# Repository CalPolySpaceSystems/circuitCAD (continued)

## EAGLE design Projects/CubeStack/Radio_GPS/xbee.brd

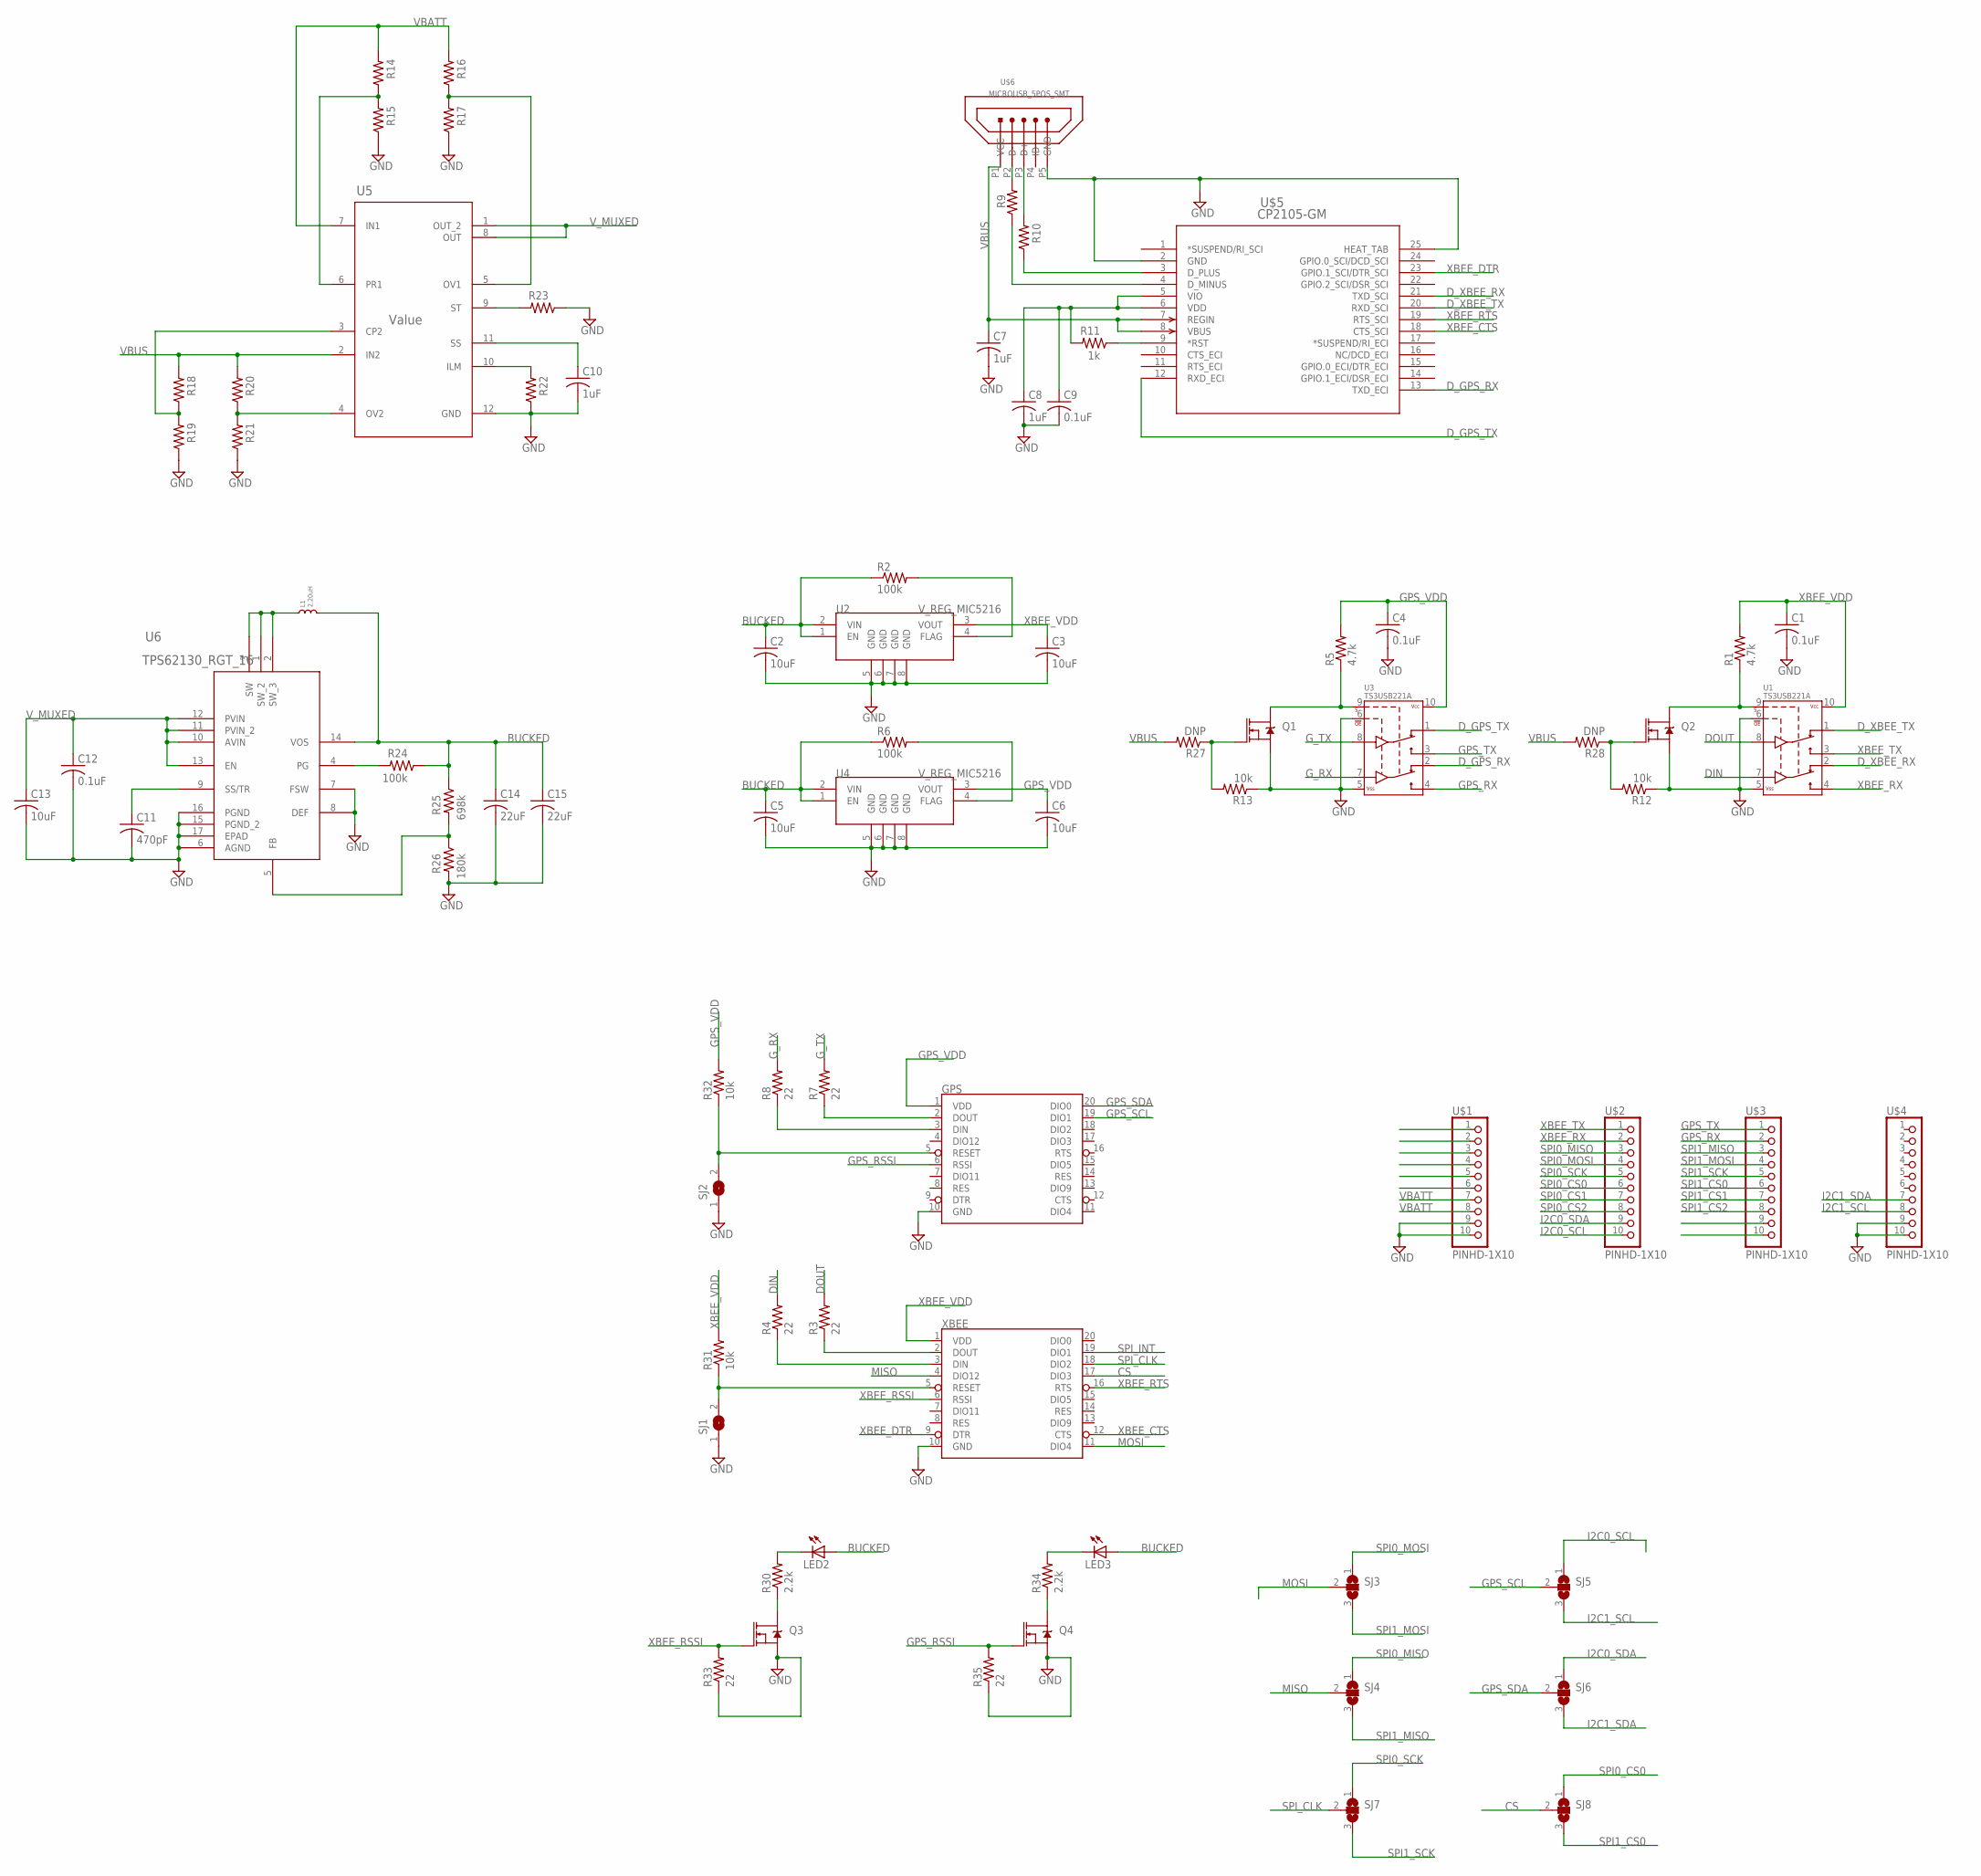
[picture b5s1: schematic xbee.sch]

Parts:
C1, C4, C9: 0.1uF; C0402
C2, C3, C5, C6, C13: 10uF; C1206
C7, C8, C10: 1uF; C0402
C11: 470pF; C0402
C12: 0.1uF; C0603
C14, C15: 22uF; C1210
GPS: XBEESMD; XBEE-SMD
L1: 2.20uH; XAL4020
LED2, LED3: LEDSML0603; SML0603
Q1, Q2, Q3, Q4: 310mA/60V/1.6Ω; SOT323
R1, R5: 4.7k; R0402
R2, R6, R24: 100k; R0402
R3, R4, R7, R8, R33, R35: 22; R0402
R9, R10, R14, R15, R16, R17, R18, R19, R20, R21, R22, R23: R-US_R0402; R0402
R11: 1k; R0402
R12, R13, R31, R32: 10k; R0402
R25: 698k; R0402
R26: 180k; R0402
R27, R28: DNP; R0402
R30, R34: 2.2k; R0402
SJ1, SJ2: SJW
SJ3, SJ4, SJ5, SJ6, SJ7, SJ8: SJ2W; SJ_2
U1, U3: TS3USB221A; QFN-10-RSE
U2, U4: V_REG_MIC5216; MSOP8
U5: Value; RUX0012A
U6: TPS62130_RGT_16; RGT16_1P7X1P7
U$1, U$2, U$3, U$4: PINHD-1X10; 1X10-BIG
U$5: CP2105-GM; QFN24_4X4
U$6: MICROUSB_5POS_SMT; RECPT_SMT_R/A
XBEE: XBEESMD; XBEE-SMD

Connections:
BUCKED: C2.1, C5.1, C14.1, C15.1, L1.2, LED2.A, LED3.A, R2.1, R6.1, R24.1, R25.1, U2.1 (EN), U2.2 (VIN), U4.1 (EN), U4.2 (VIN), U6.14 (VOS)
CS: SJ8.2, XBEE.17 (DIO3)
DIN: R4.2, U1.7 (D-)
DOUT: R3.2, U1.8 (D+)
D_GPS_RX: U3.2 (1D-), U$5.13 (TXD_ECI)
D_GPS_TX: U3.1 (1D+), U$5.12 (RXD_ECI)
D_XBEE_RX: U1.2 (1D-), U$5.21 (TXD_SCI)
D_XBEE_TX: U1.1 (1D+), U$5.20 (RXD_SCI)
GND: C1.2, C2.2, C3.2, C4.2, C5.2, C6.2, C7.2, C8.2, C9.2, C10.2, C11.2, C12.2, C13.2, C14.2, C15.2, GPS.10 (GND), Q1.2 (S), Q2.2 (S), Q3.2 (S), Q4.2 (S), R12.1, R13.1, R15.1, R17.1, R19.1, R21.1, R22.1, R23.1, R26.2, R33.1, R35.1, SJ1.1, SJ2.1, U1.5 (VSS), U1.6 (!OE), U2.5 (GND), U2.6 (GND), U2.7 (GND), U2.8 (GND), U3.5 (VSS), U3.6 (!OE), U4.5 (GND), U4.6 (GND), U4.7 (GND), U4.8 (GND), U5.12 (GND), U6.6 (AGND), U6.7 (FSW), U6.8 (DEF), U6.15 (PGND_2), U6.16 (PGND), U6.17 (EPAD), U$1.9, U$1.10, U$4.9, U$4.10, U$5.2 (GND), U$5.25 (HEAT_TAB), U$6.P5 (GND), XBEE.10 (GND)
GPS_RSSI: GPS.6 (RSSI), Q4.1 (G), R35.2
GPS_RX: U3.4 (2D-), U$3.2
GPS_SCL: GPS.19 (DIO1), SJ5.2
GPS_SDA: GPS.20 (DIO0), SJ6.2
GPS_TX: U3.3 (2D+), U$3.1
GPS_VDD: C4.1, C6.1, GPS.1 (VDD), R5.2, R32.2, U3.10 (VCC), U4.3 (VOUT)
G_RX: R8.2, U3.7 (D-)
G_TX: R7.2, U3.8 (D+)
I2C0_SCL: SJ5.1, U$2.10
I2C0_SDA: SJ6.1, U$2.9
I2C1_SCL: SJ5.3, U$4.8
I2C1_SDA: SJ6.3, U$4.7
MISO: SJ4.2, XBEE.4 (DIO12)
MOSI: SJ3.2, XBEE.11 (DIO4)
unnamed: R2.2, U2.4 (FLAG)
unnamed: R3.1, XBEE.2 (DOUT)
unnamed: R4.1, XBEE.3 (DIN)
unnamed: R6.2, U4.4 (FLAG)
unnamed: GPS.2 (DOUT), R7.1
unnamed: GPS.3 (DIN), R8.1
unnamed: R9.2, U$6.P2 (D-)
unnamed: R10.2, U$6.P3 (D+)
unnamed: R10.1, U$5.3 (D_PLUS)
unnamed: R9.1, U$5.4 (D_MINUS)
unnamed: R22.2, U5.10 (ILM)
unnamed: C8.1, C9.1, R11.2, U$5.5 (VIO), U$5.6 (VDD)
unnamed: Q1.3 (D), R5.1, U3.9 (S)
unnamed: Q2.3 (D), R1.1, U1.9 (S)
unnamed: R11.1, U$5.9 (*RST)
unnamed: R14.1, R15.2, U5.6 (PR1)
unnamed: R16.1, R17.2, U5.5 (OV1)
unnamed: R18.1, R19.2, U5.3 (CP2)
unnamed: R20.1, R21.2, U5.4 (OV2)
unnamed: C11.1, U6.9 (SS/TR)
unnamed: C10.1, U5.11 (SS)
unnamed: Q1.1 (G), R13.2, R27.1
unnamed: R23.2, U5.9 (ST)
unnamed: R25.2, R26.1, U6.5 (FB)
unnamed: Q2.1 (G), R12.2, R28.1
unnamed: R24.2, U6.4 (PG)
unnamed: L1.1, U6.1 (SW_2), U6.2 (SW_3), U6.3 (SW)
unnamed: LED2.C, R30.2
unnamed: Q3.3 (D), R30.1
unnamed: Q4.3 (D), R34.1
unnamed: LED3.C, R34.2
unnamed: R31.1, SJ1.2, XBEE.5 (RESET)
unnamed: GPS.5 (RESET), R32.1, SJ2.2
SPI0_CS0: SJ8.1, U$2.6
SPI0_CS1: U$2.7
SPI0_CS2: U$2.8
SPI0_MISO: SJ4.1, U$2.3
SPI0_MOSI: SJ3.1, U$2.4
SPI0_SCK: SJ7.1, U$2.5
SPI1_CS0: SJ8.3, U$3.6
SPI1_CS1: U$3.7
SPI1_CS2: U$3.8
SPI1_MISO: SJ4.3, U$3.3
SPI1_MOSI: SJ3.3, U$3.4
SPI1_SCK: SJ7.3, U$3.5
SPI_CLK: SJ7.2, XBEE.18 (DIO2)
SPI_INT: XBEE.19 (DIO1)
VBATT: R14.2, R16.2, U5.7 (IN1), U$1.7, U$1.8
VBUS: C7.1, R18.2, R20.2, R27.2, R28.2, U5.2 (IN2), U$5.7 (REGIN), U$5.8 (VBUS), U$6.P1 (VCC)
V_MUXED: C12.1, C13.1, U5.1 (OUT_2), U5.8 (OUT), U6.10 (AVIN), U6.11 (PVIN_2), U6.12 (PVIN), U6.13 (EN)
XBEE_CTS: U$5.18 (CTS_SCI), XBEE.12 (CTS)
XBEE_DTR: U$5.23 (GPIO.1_SCI/DTR_SCI), XBEE.9 (DTR)
XBEE_RSSI: Q3.1 (G), R33.2, XBEE.6 (RSSI)
XBEE_RTS: U$5.19 (RTS_SCI), XBEE.16 (RTS)
XBEE_RX: U1.4 (2D-), U$2.2
XBEE_TX: U1.3 (2D+), U$2.1
XBEE_VDD: C1.1, C3.1, R1.2, R31.2, U1.10 (VCC), U2.3 (VOUT), XBEE.1 (VDD)

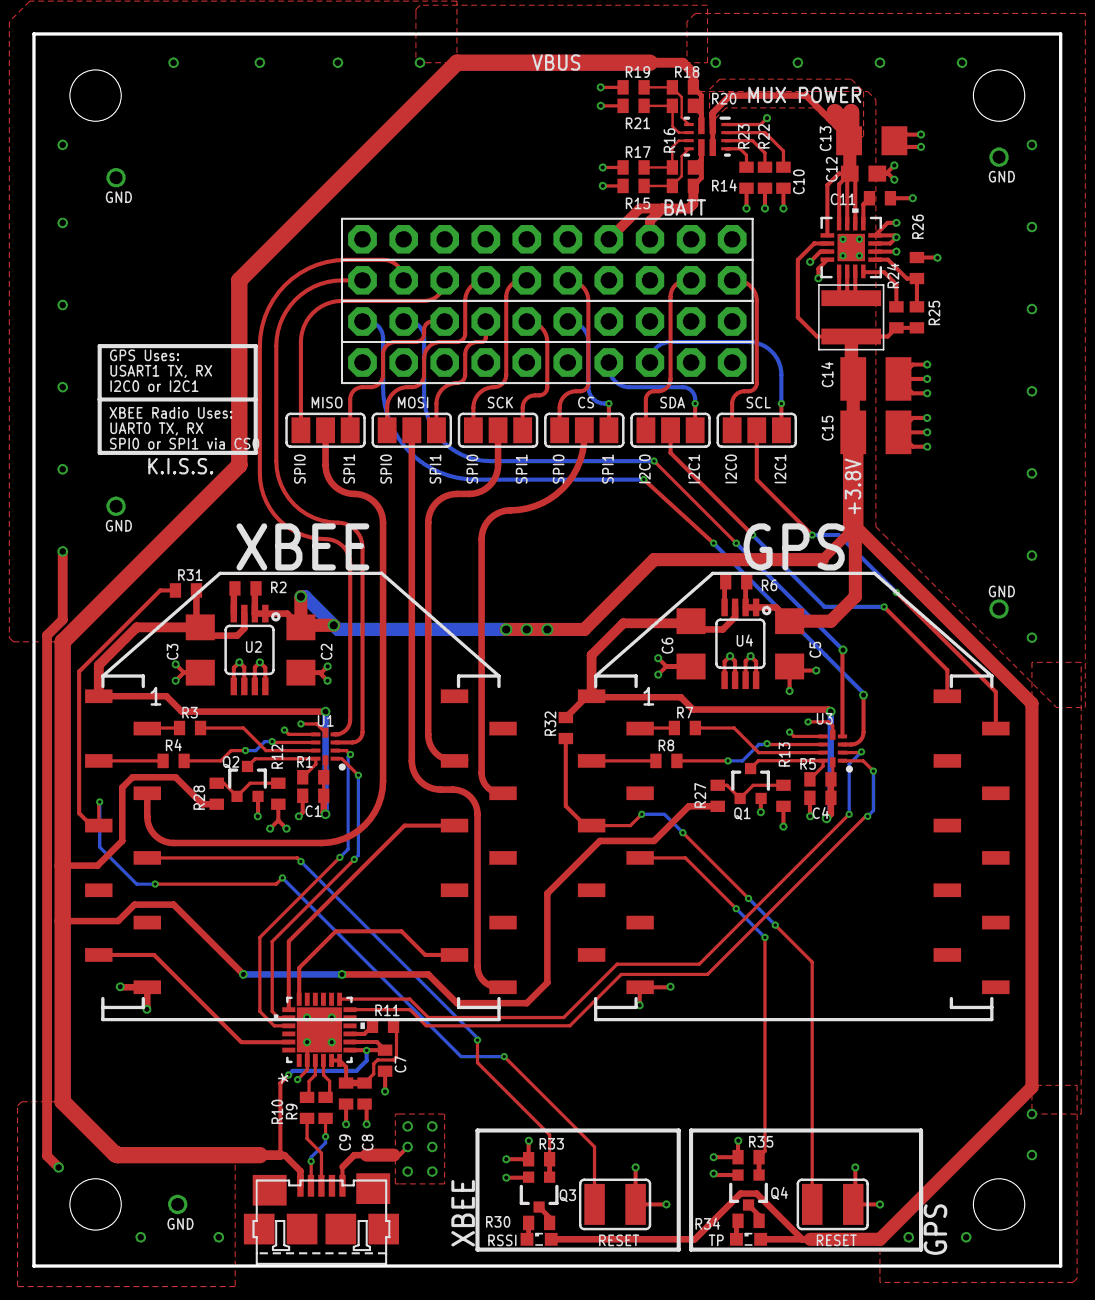
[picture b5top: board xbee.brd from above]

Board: 2 copper layers, 63.5 x 76.2 mm, 78 parts (0 on the bottom side), 75 nets.

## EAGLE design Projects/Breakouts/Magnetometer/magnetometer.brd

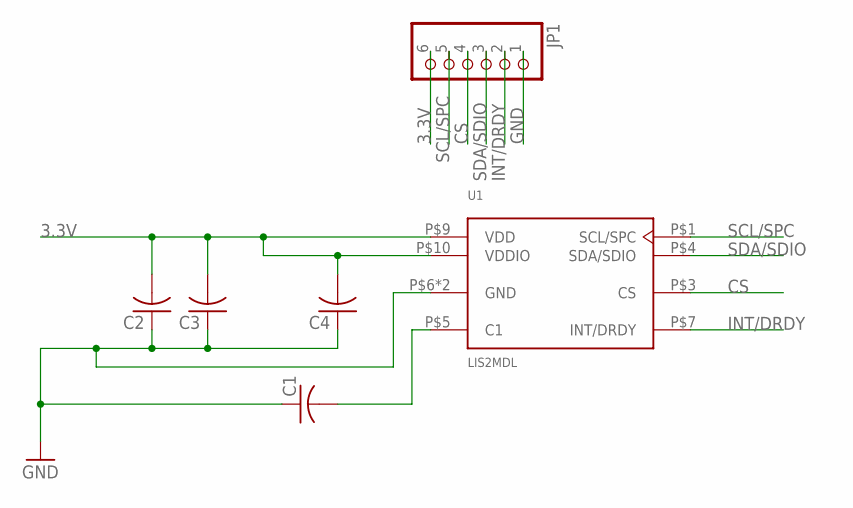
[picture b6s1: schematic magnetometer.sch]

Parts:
C1, C2, C3, C4: C-USC0805; C0805
JP1: PINHD-1X6; 1X06
U1: LIS2MDL; LGA-12

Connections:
3.3V: C2.2, C3.2, C4.2, JP1.6, U1.P$9 (VDD), U1.P$10 (VDDIO)
C1: C1.2, U1.P$5 (C1)
CS: JP1.4, U1.P$3 (CS)
GND: C1.1, C2.1, C3.1, C4.1, JP1.1, U1.P$6 (GND), U1.P$8 (GND)
INT/DRDY: JP1.2, U1.P$7 (INT/DRDY)
SCL/SPC: JP1.5, U1.P$1 (SCL/SPC)
SDA/SDIO: JP1.3, U1.P$4 (SDA/SDIO)

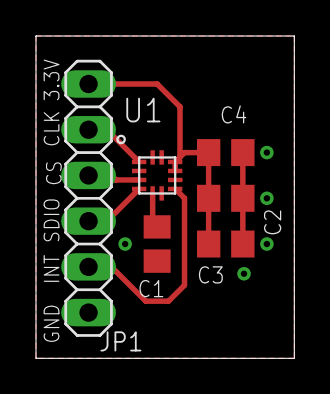
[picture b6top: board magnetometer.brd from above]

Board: 2 copper layers, 14.4 x 17.9 mm, 6 parts (0 on the bottom side), 7 nets.

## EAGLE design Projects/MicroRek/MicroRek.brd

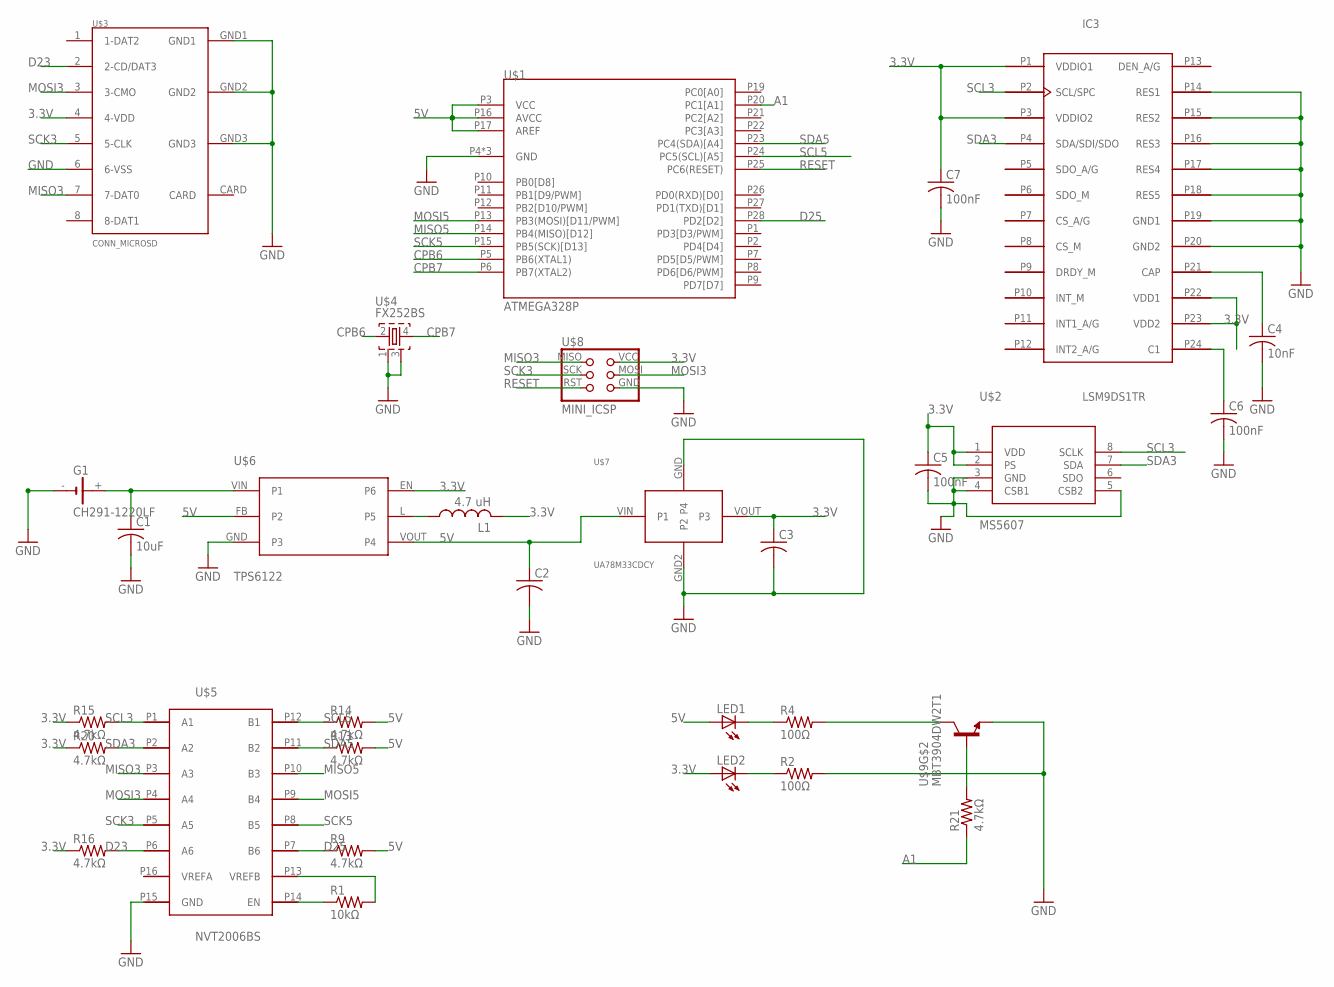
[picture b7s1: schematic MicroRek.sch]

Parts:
C1: 10uF; C0402
C2, C3: C-USC0402; C0402
C4: 10nF; C0402
C5, C6, C7: 100nF; C0402
G1: CH291-1220LF
IC3: LSM9DS1TR; LGA
L1: 4.7 uH; MICROREK_INDUCTOR
LED1, LED2: LEDCHIPLED_0805; CHIPLED_0805
R1: 10kΩ; R0603
R2, R4: 100Ω; R0603
R9, R13, R14, R15, R16, R20, R21: 4.7kΩ; R0603
U$1: ATMEGA328P; VQFN-28
U$2: MS5607; 8-QFN
U$3: CONN_MICROSD
U$4: FX252BS; FA-20H
U$5: NVT2006BS; HVQFN16
U$6: TPS6122; TPS6122P
U$7: UA78M33CDCY; DCY
U$8: MINI_ICSP; NPNN032FFKS-RC
U$9: MBT3904DW2T1; SOT-363

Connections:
3.3V: C3.1, C5.1, C7.1, IC3.P1 (VDDIO1), IC3.P3 (VDDIO2), IC3.P22 (VDD1), IC3.P23 (VDD2), L1.P$2 (2), LED2.A, R15.1, R16.1, R20.1, U$2.1 (VDD), U$2.2 (PS), U$3.4 (4-VDD), U$6.EN (P6), U$7.VOUT (P3), U$8.VCC (2)
5V: C2.1, LED1.A, R9.2, R13.2, R14.2, U$1.P3 (VCC), U$1.P16 (AVCC), U$1.P17 (AREF), U$6.FB (P2), U$6.VOUT (P4), U$7.VIN (P1)
A1: R21.1, U$1.P20 (PC1[A1])
CPB6: U$1.P5 (PB6(XTAL1)), U$4.2 (1)
CPB7: U$1.P6 (PB7(XTAL2)), U$4.4 (3)
D23: R16.2, U$3.2 (2-CD/DAT3), U$5.P6 (A6)
D25: R9.1, U$1.P28 (PD2[D2]), U$5.P7 (B6)
GND: C1.2, C2.2, C3.2, C4.2, C5.2, C6.2, C7.2, G1.-, IC3.P14 (RES1), IC3.P15 (RES2), IC3.P16 (RES3), IC3.P17 (RES4), IC3.P18 (RES5), IC3.P19 (GND1), IC3.P20 (GND2), R2.2, U$1.P4 (GND), U$1.P18 (GND), U$1.TH (GND), U$2.3 (GND), U$2.4 (CSB1), U$2.5 (CSB2), U$3.6 (6-VSS), U$3.GND1, U$3.GND2, U$3.GND3, U$4.1 (2), U$4.3 (4), U$5.P15 (GND), U$6.GND (P3), U$7.GND (P4), U$7.GND2 (P2), U$8.GND (6), U$9.P$6 (E)
MISO3: U$3.7 (7-DAT0), U$5.P3 (A3), U$8.MISO (1)
MISO5: U$1.P14 (PB4(MISO)[D12]), U$5.P10 (B3)
MOSI3: U$3.3 (3-CMO), U$5.P4 (A4), U$8.MOSI (4)
MOSI5: U$1.P13 (PB3(MOSI)[D11/PWM]), U$5.P9 (B4)
unnamed: R1.1, U$5.P14 (EN)
unnamed: C1.1, G1.+, U$6.VIN (P1)
unnamed: L1.P$1 (1), U$6.L (P5)
unnamed: C4.1, IC3.P21 (CAP)
unnamed: C6.1, IC3.P24 (C1)
unnamed: LED1.C, R4.1
unnamed: R4.2, U$9.P$5 (C)
unnamed: LED2.C, R2.1
unnamed: R21.2, U$9.P$1 (B)
RESET: U$1.P25 (PC6(RESET)), U$8.RST (5)
SCK3: U$3.5 (5-CLK), U$5.P5 (A5), U$8.SCK (3)
SCK5: U$1.P15 (PB5(SCK)[D13]), U$5.P8 (B5)
SCL3: IC3.P2 (SCL/SPC), R15.2, U$2.8 (SCLK), U$5.P1 (A1)
SCL5: R14.1, U$1.P24 (PC5(SCL)[A5]), U$5.P12 (B1)
SDA3: IC3.P4 (SDA/SDI/SDO), R20.2, U$2.7 (SDA), U$5.P2 (A2)
SDA5: R13.1, U$1.P23 (PC4(SDA)[A4]), U$5.P11 (B2)
VREFB: R1.2, U$5.P13 (VREFB)

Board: 2 copper layers, 31 parts (2 on the bottom side), 29 nets, no tracks yet.

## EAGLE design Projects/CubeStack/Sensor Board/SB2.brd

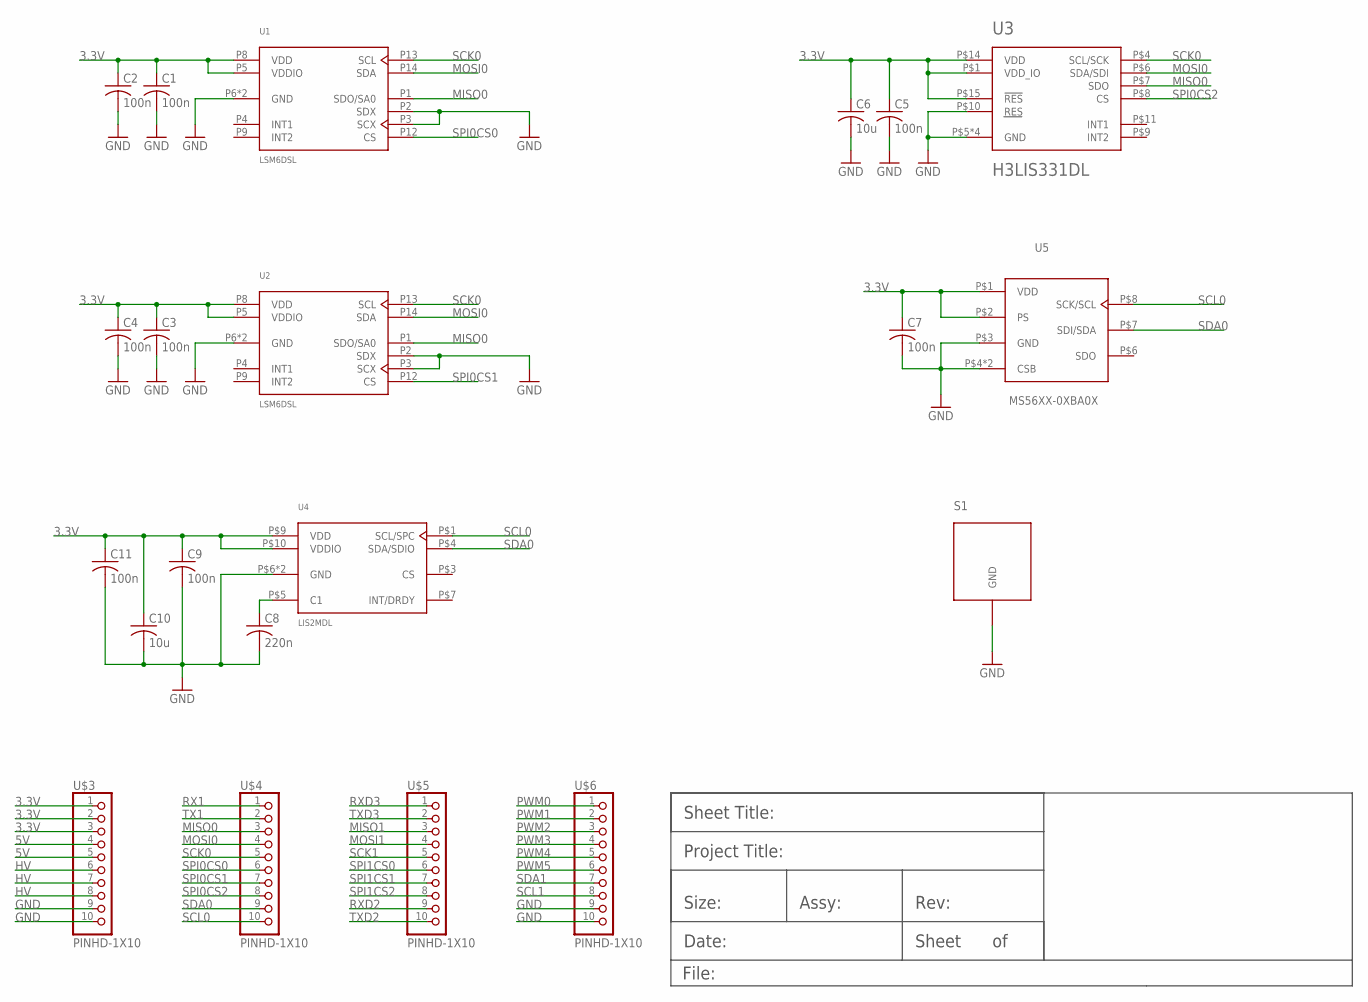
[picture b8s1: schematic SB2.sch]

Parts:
C1, C2, C3, C4, C5, C7, C9, C11: 100n; C0805
C6, C10: 10u; C0805
C8: 220n; C0805
S1: EMI_SHIELD; BMI-S-210
U1, U2: LSM6DSL; LGA-14
U3: H3LIS331DL; TFLGA-16L
U4: LIS2MDL; LGA-12
U5: MS56XX-0XBA0X; MS56XX
U$3, U$4, U$5, U$6: PINHD-1X10; 1X10-BIG

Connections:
3.3V: C1.1, C2.1, C3.1, C4.1, C5.1, C6.1, C7.1, C9.1, C10.1, C11.1, U1.P5 (VDDIO), U1.P8 (VDD), U2.P5 (VDDIO), U2.P8 (VDD), U3.P$1 (VDD_IO), U3.P$14 (VDD), U3.P$15 (!RES), U4.P$9 (VDD), U4.P$10 (VDDIO), U5.P$1 (VDD), U5.P$2 (PS), U$3.1, U$3.2, U$3.3
5V: U$3.4, U$3.5
GND: C1.2, C2.2, C3.2, C4.2, C5.2, C6.2, C7.2, C8.2, C9.2, C10.2, C11.2, S1.P$1, S1.P$2, S1.P$3, S1.P$4, S1.P$5, S1.P$6, S1.P$7, S1.P$8, S1.P$9, S1.P$10, S1.P$11, S1.P$12, S1.P$13, S1.P$14, S1.P$15, S1.P$16, S1.P$17, S1.P$18, S1.P$19, S1.P$20, S1.P$21, S1.P$22, S1.P$23, S1.P$24, S1.P$25, S1.P$26, S1.P$27, S1.P$28, U1.P2 (SDX), U1.P3 (SCX), U1.P6 (GND), U1.P7 (GND), U2.P2 (SDX), U2.P3 (SCX), U2.P6 (GND), U2.P7 (GND), U3.P$5 (GND), U3.P$10 (RES), U3.P$12 (GND), U3.P$13 (GND), U3.P$16 (GND), U4.P$6 (GND), U4.P$8 (GND), U5.P$3 (GND), U5.P$4 (CSB), U5.P$5 (CSB), U$3.9, U$3.10, U$6.9, U$6.10
HV: U$3.6, U$3.7, U$3.8
MISO0: U1.P1 (SDO/SA0), U2.P1 (SDO/SA0), U3.P$7 (SDO), U$4.3
MISO1: U$5.3
MOSI0: U1.P14 (SDA), U2.P14 (SDA), U3.P$6 (SDA/SDI), U$4.4
MOSI1: U$5.4
unnamed: C8.1, U4.P$5 (C1)
PWM0: U$6.1
PWM1: U$6.2
PWM2: U$6.3
PWM3: U$6.4
PWM4: U$6.5
PWM5: U$6.6
RX1: U$4.1
RXD2: U$5.9
RXD3: U$5.1
SCK0: U1.P13 (SCL), U2.P13 (SCL), U3.P$4 (SCL/SCK), U$4.5
SCK1: U$5.5
SCL0: U4.P$1 (SCL/SPC), U5.P$8 (SCK/SCL), U$4.10
SCL1: U$6.8
SDA0: U4.P$4 (SDA/SDIO), U5.P$7 (SDI/SDA), U$4.9
SDA1: U$6.7
SPI0CS0: U1.P12 (CS), U$4.6
SPI0CS1: U2.P12 (CS), U$4.7
SPI0CS2: U3.P$8 (CS), U$4.8
SPI1CS0: U$5.6
SPI1CS1: U$5.7
SPI1CS2: U$5.8
TX1: U$4.2
TXD2: U$5.10
TXD3: U$5.2

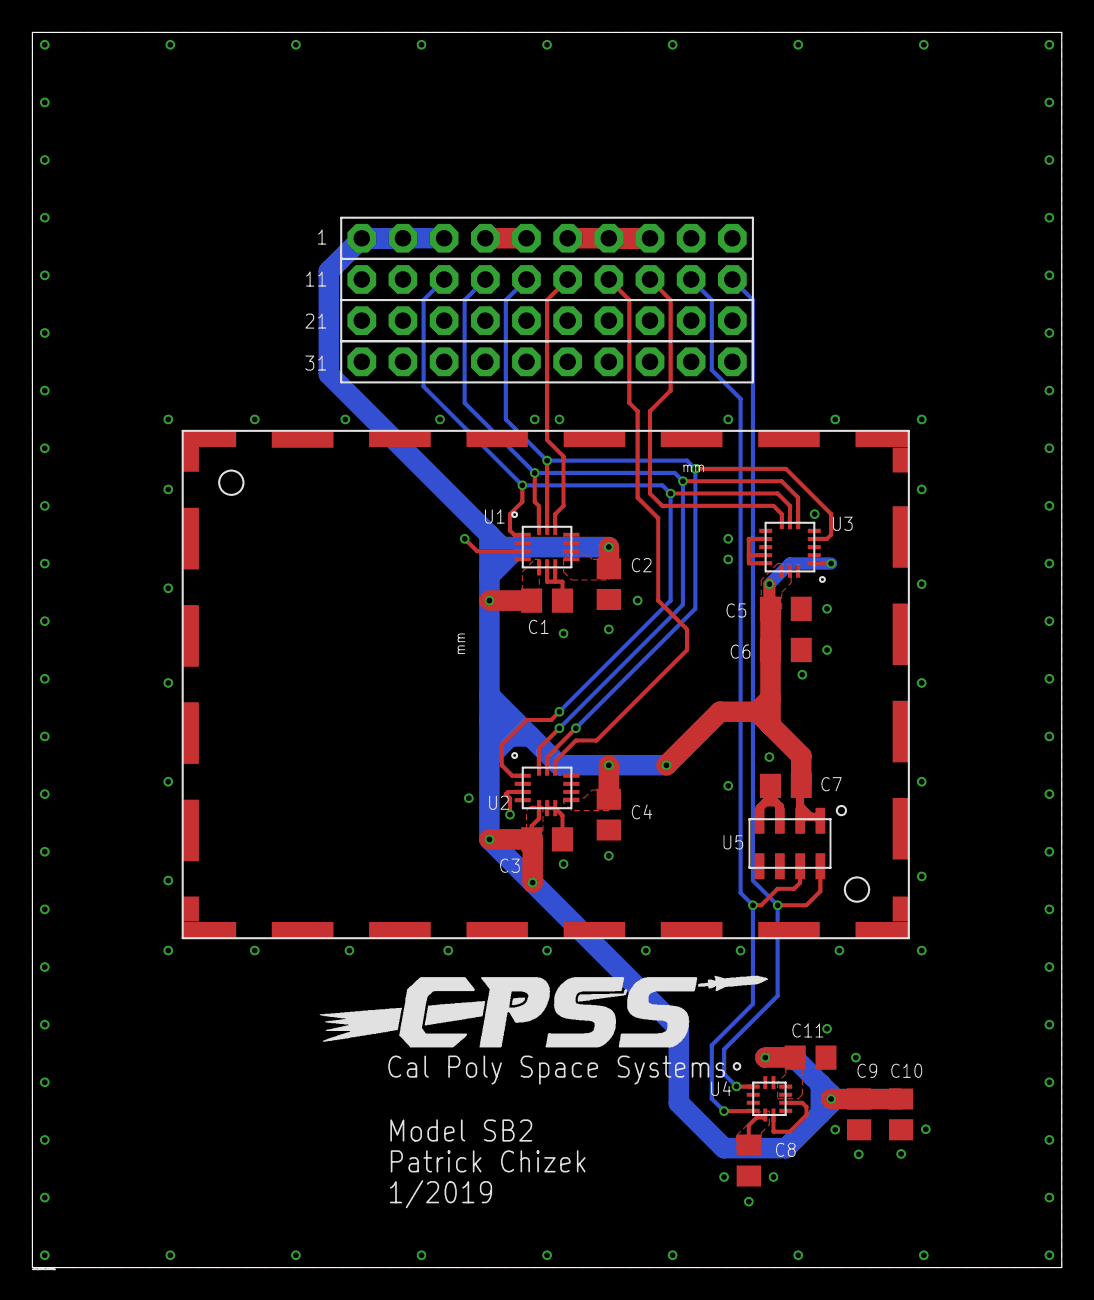
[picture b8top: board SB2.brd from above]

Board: 2 copper layers, 63.5 x 76.2 mm, 21 parts (0 on the bottom side), 13 nets.

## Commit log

2017-09-24 Committed Josh's IMU to Repository
2017-09-24 Added Patch Circles to highlight areas to be revised
2017-09-29 Revised overly complicated power system
2017-10-10 Simplified power system
2017-10-10 Re-centered Dimensions
2017-10-12 Added CAM file section for UBX
2017-10-12 Finished labeling, removed SPI pull ups
2017-10-12 Fixed Labelling
2017-10-12 Added schematic for UpBoard X in planned configuration
2017-10-21 Initial Commit of the Radio Board
    Radio board PCB and schematic of Rev 1. Datasheets and BOM still to be added.
2017-10-22 Added BOM and PCB GND connections for crystal
2017-10-25 Final Update of Radio Board
    Modified existing silkscreen with name and description on board.
2017-10-26 Add strain gauge board files
    Schematic and most of layout
2017-10-30 First fixes, schematic appearance changes
    Connected D+ line on native USB port. Added title block and reorganized
    schematic to fit on a size C sheet. Revision number is now 1.
2017-10-30 Added R1 PDF Schematic
2017-10-30 Created Readme
2017-10-30 Reorganized Circuit CAD
2017-10-31 Organized power supply into own module
2017-11-03 Sheet Changes
2018-01-13 Added Power Distro
2018-01-13 Added folder
2018-01-30 Added I2C data line
2018-02-10 Created MicroRek Folder
2018-02-10 Revert "Added I2C data line"
    This reverts commit ce24847924fb5b1688f37034ce33982163fc9d56.
2018-02-10 Wired Barometer
2018-02-10 Updated Schematic/Created Board
2018-02-11 Added frame, replaced ATMEGA328P part
2018-02-13 Add git support for CPSS libraries
2018-02-19 Remove EAGLE generated backups
2018-02-19 Add more IC parts
2018-02-19 Pre-Autorouter Commit
2018-02-22 Update R1
2018-02-24 Connected Flash corrctly, changed sheet size
2018-02-26 Finished routing traces, front silkscreen.
2018-02-27 Fixed refdes
2018-02-27 update libraries
2018-02-27 Updated LED drivers
2018-02-28 Added in and routed bjt arrays
2018-02-28 New bjt array
2018-02-28 Fixed naming and silkscreen
2018-03-07 Schemtics and bords
2018-03-07 created and finished upboard radio adapter
2018-03-07 Changed transistors
2018-03-10 Worked on MicroRek Board Still needs lots of work
2018-03-31 Rewiring on Microrek
2018-04-02 Updated MicroRek Board Layout
2018-04-03 updated board
2018-04-05 updated board layout
2018-04-07 LOTS of work on board layout
2018-04-07 Added mini ICSP part
2018-04-09 Added CAM Files for UBXR1 and Adapters
2018-04-12 Added pdf document of UBXR1
2018-04-12 Removed EAGLE backups
2018-04-12 Edit title block
2018-04-21 MicroRek Updates
    Changed inductor package
    Fixed some wiring
    Fixed Crystal wiring (MAYBE)
    Will work more in the morning
2018-05-05 Board Updates
2018-05-08 MicroRek Update
    Added pullup resistors and the mini icsp port
2018-05-15 Added LED's
2018-05-16 small led nd pullup update
2018-05-17 fixed pullup resistors
2018-05-17 Approved Final Schematic
2018-05-19 started new board layout
2018-06-18 Oversized beacon PCB files
    Initial upload of KiCAD design file for a 222.25 to 223.29 MHz single tone transmitter. Uses the ADF4360-8 PLL and has an SPI breakout for control. All parts oversized to 0805 or larger for newbies t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
2018-06-19 Mini Rek Upload
    Like the micro rek but with onboard transmitter. It's a little larger though
2018-06-19 Basic power regulation schematic
2018-06-19 Added PDF outputs and cleaned up schematic
2018-07-15 Work on CubeStack/Stackup
2018-07-15 Added some new parts
2018-07-16 Added intial schematics for pressure board rev 2
2018-08-25 Basic BOM, no parts just footprints and quantities
2018-09-03 PDF of schematic
2018-09-03 Mini Rek Gerbers
2018-09-03 Mini Rek Gerbers Reupload
2018-09-16 First Draft of SAM3X CPU Core
2018-11-10 Modified Libraries, Worked on STM32F3 Core
2018-11-10 Fixed CAD Directories
2018-11-10 Fixed libraries I think
2018-11-11 Routed PWM, GPIO lines
2018-11-14 Added LIS2MDL and LSM6DSL, improved parts
2018-12-20 Removed Feature Drawing examples
2018-12-20 Updated libraries, added EMI shield part
2018-12-20 Completed STM32 Core to be Reviewed
2018-12-20 Schematic and Layout of Sensor Board
    TODO: Fix silkscreen and organize schematic.
2018-12-20 Depricated old Due CPU Core design
2018-12-20 Modified Existing SAM3X CPU for New Bus Pinout
2018-12-21 Added radio board and component libraries
2018-12-22 Added Via Stitching to Perimeter + Bus Pin Numbers
2018-12-22 Organized Silkscreen + Added Bus Pin Numbers
2019-01-02 Created Power Distribution Board with FET Array
    TODO: Change component names
2019-01-02 Update component names
    TODO: Change Resistor/Capacitor names
2019-01-02 Added Connectors and Regulators
2019-01-18 Reorganized CircuitCAD Repo
    Divided into two sections: dependencies and projects. See readmes in each directory for more info
2019-01-18 Put all design blocks and cam jobs into "Resources"
2019-01-18 Created CAM job for ordering from JLCPCB
2019-01-19 Add files via upload
    This folder will contain breakout boards.
2019-01-27 Create Test Code for Arduino Over SPI
2019-01-27 Add files via upload
    This is the EAGLE schematic for the pressure sensor board.
2019-01-27 Rename Projects/Breakouts/Magnetometer/Test Code for Arduino Over SPI to Projects/Breakouts/Test Code for Arduino Over SPI
2019-02-16 Added updated radio GPS board
2019-03-16 Added some part values
2019-03-19 Create SAMD21 CPU.brd
    Finished SAMD21 CPU Design
2019-03-19 Changed C9 package
2019-03-19 Added more vias to SAMD21 Core
2019-07-24 Delete Test Code for Arduino Over SPI
    file unnecessary
2020-01-11 Added Ptap circuit CAD files
2020-01-11 Added PTAP circuit CAD
2020-01-18 Upload of DVR-VTX and PDU2 files
